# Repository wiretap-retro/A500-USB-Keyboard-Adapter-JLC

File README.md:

# A500 USB Keyboard Adapter JLC
A USB keyboard adapter for the Amiga 500 based on a simplified RP2040 design for JLCPCB Assembly

## Intro
This is a USB keyboard adapter I designed a board for to use in my Amiga 500 tower or bench testing. It is based on the amigahid-pico firmware by borb (nine). The KiCAD files, Gerbers, and BOM are in this repository, as well as the JLCPCB BOM and Pick'n'Place CPL files. The completed board attaches to the A500's keyboard header and provides a USB pin header for your interface device. On my build, I used a pin header to female USB Type A cable that screws into in the rear of my case on a PCI bracket.

Demo Video: https://youtu.be/7yw0AOvhLqg  (original board shown, this repository is an updated/simplified design for JLCPCB assembly)

## Parts
* In the Master BOM file, order the parts needed for hand soldering only. JLCPBC will do all the tough surface mount work. With 5 assembled boards, it comes out to roughly $15 each with shipping. (cheapest options / slow boat shipping)

## Building the Adapter
* Use JLCPCB's assembly service -- Upload the gerber files, choose your board color, and specify the Remove Order Number field as "Provided by Customer".
* Select the PCB Assembly slider and ensure you want either 2 or 5 boards assembled (top side only) and click confirm. Leave all other settings as-is.
* Click next at the board preview.
* On the Bill of Materials page, upload the BOM from the JLCPCB folder in this repo, as well as the Pick-n-Place CPL file. Click "Process BOM & CPL".
* Check to make sure all parts are available and click next, otherwise you have to substitute parts if a compatible part is in stock. (fit/form/function) Click next.
* On the Component Placement screen, ensure all parts are oriented and placed properly. Pay attention to Pin 1 on the chips. Click next.
* Choose the product type -- I recommend selecting "DIY". Save to cart and process your order. You may have to speak with JLCPCB to confirm your component placements via Email before they fully process it.
* Wait for your board to arrive.
* Solder the hand soldered components onto the board in their appropriate locations.

## Flashing the Firmware
First off, a huge thank you to Nine for developing the amigahid-pico, as this design uses its firmware. Firmware is located at: https://github.com/borb/amigahid-pico/
1. Build the firmware per the instructions at https://github.com/borb/amigahid-pico/blob/main/doc/installation.md
2. Hold the BOOT button.
3. Plug a MicroUSB cable to the PCB's MicroUSB port and plug the other end into the PC you just compiled the firmware on. It will then show up as a mass storage device.
4. Release the BOOT button.
5. Copy the amigahid-pico.uf2 file from the "build/src/" directory you compiled to the RP2040's mounted USB storage volume. It will then disconnect/reset.
6. Disconnect the USB cable from the PC and keyboard adapter PCB.

## Installation into the Amiga
1. Gain access to your Amiga 500 motherboard.
2. Disconnect the keyboard if it is still connected.
3. Plug the PCB into the A500's keyboard header either the Type A or Type B socket. For reference my Amiga 500 Rev 6A needed Type A.
4. Plug your USB cable into the pin header. Pay close attention to the orientation of the leads.
5. Plug the keyboard or wireless keyboard adapter into the other end of the USB cable. Don't use a blinding LED backlit keyboard that uses >500mA, as you don't want to smoke your traces.
6. Boot the Amiga and test it out!

## Optional Stuff
* If using a tower case, you can plug in the Power LED and HDD LED to the pin headers on the PCB to show the status indications.
* USB HID mouse support is included in Nine's firmware, but none of the mice I used would work with it. I use a DB9 connected OpenLaserMouse anyway, but maybe you'll have better luck testing various mice to see if one works. I know the firmware is still an in-progress project, or maybe I didn't do something right when I compiled the firmware. 
* Amiga keys are currently mapped to right and left windows keys. Before compiling the firmware, you can modify those keys if necessary at your own discretion.
* Reset is initiated by Left Ctrl + Left Win + Right Win (CTRL + AMIGA + AMIGA)

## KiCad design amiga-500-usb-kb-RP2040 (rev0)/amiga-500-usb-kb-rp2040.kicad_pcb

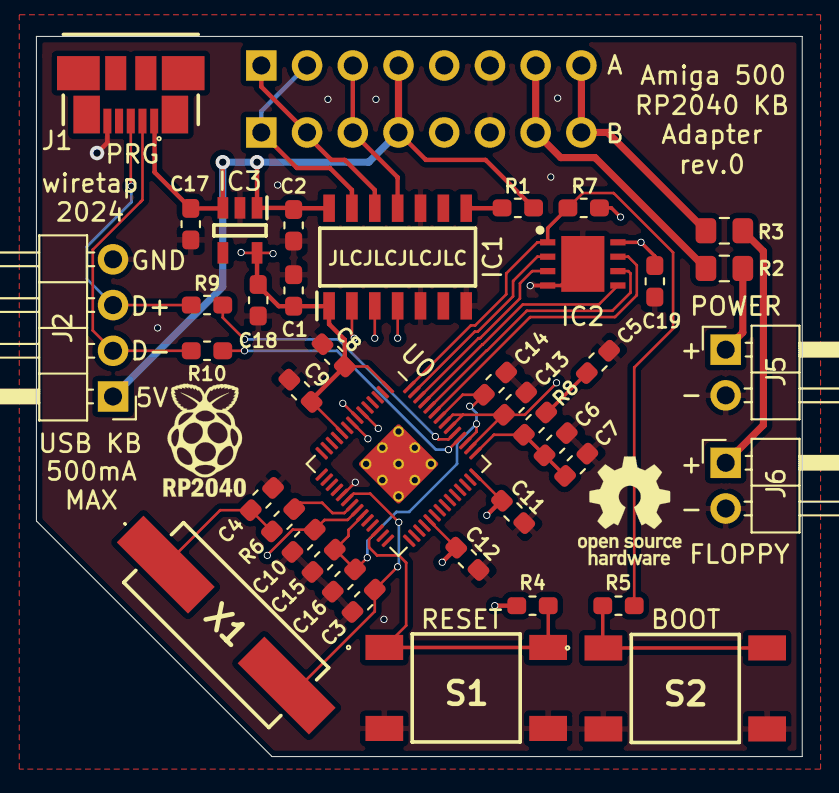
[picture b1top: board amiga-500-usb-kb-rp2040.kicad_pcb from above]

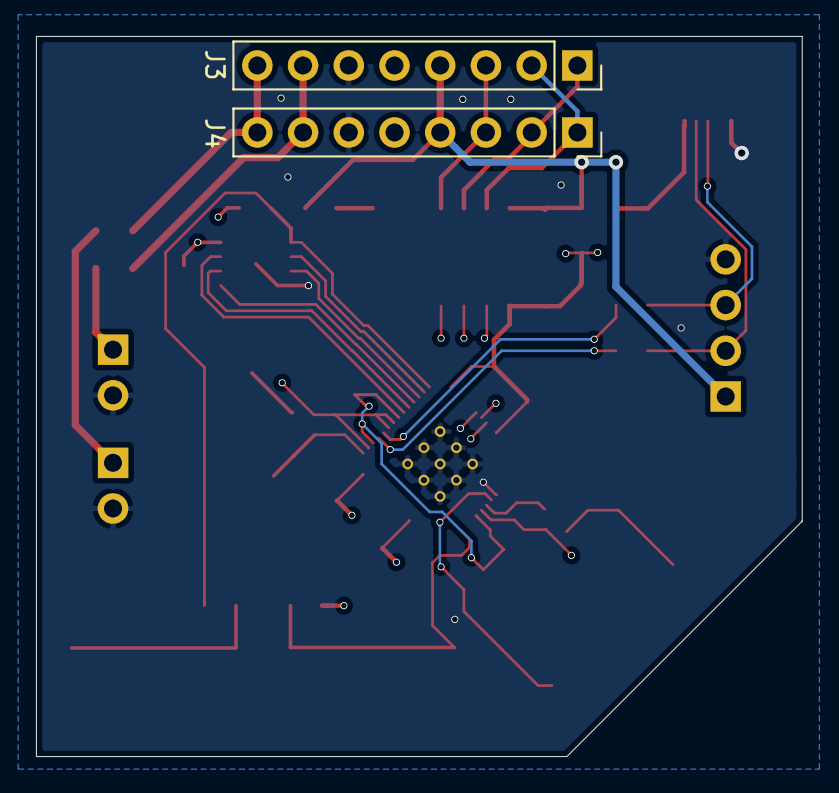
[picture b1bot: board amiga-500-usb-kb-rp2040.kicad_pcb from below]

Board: 4 copper layers, 42.5 x 40.0 mm, 42 parts (2 on the bottom side), 32 nets.

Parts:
C1, C2, C5, C6, C8, C9, C10, C11, C12, C14, C15, C19: 0.1uF; C_0603_1608Metric_Pad1.05x0.95mm_HandSolder
C3, C4: 27pF; C_0603_1608Metric_Pad1.05x0.95mm_HandSolder
C7, C13, C16, C17, C18: 1uF; C_0603_1608Metric_Pad1.05x0.95mm_HandSolder
IC1: TXS0104ED; SOIC127P600X175-14N
IC2: W25Q64JVXGIQ_TR; SON80P400X400X50-9N
IC3: TPS7A2033PDBVR; SOT95P280X145-5N
J1: 47346-0001
J2: USB_HEADER; PinHeader_1x04_P2.54mm_Horizontal
J3: Type A; PinSocket_1x08_P2.54mm_Vertical
J4: Type B; PinSocket_1x08_P2.54mm_Vertical
J5: Power LED; PinHeader_1x02_P2.54mm_Horizontal
J6: Floppy LED; PinHeader_1x02_P2.54mm_Horizontal
R1, R4, R7: 10k; R_0603_1608Metric_Pad1.05x0.95mm_HandSolder
R2, R3: 1k; R_0805_2012Metric_Pad1.15x1.40mm_HandSolder
R5, R6: 1k; R_0603_1608Metric_Pad1.05x0.95mm_HandSolder
R8, R9, R10: 27; R_0603_1608Metric_Pad1.05x0.95mm_HandSolder
S1, S2: FSM2JSMAATR; FSM2J_1
U0: RP2040; RP2040-QFN-56
X1: ABLS-12MHZ-B4-T; ABLS

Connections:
+3V3: C1.1, C8.1, C9.1, C10.1, C11.1, C12.1, C13.1, C18.1, C19.1, IC1.1, IC2.8, IC3.5, R4.1, R7.1, U0.1, U0.10, U0.22, U0.33, U0.42, U0.44, U0.48, U0.49
+5V: C2.2, C17.1, IC1.14, IC3.1, IC3.3, J1.1, J2.1, J3.4, J4.4, R1.1
FLOPPY_LED: J3.8, J4.8, R3.2
GND: C1.2, C2.1, C3.2, C4.2, C5.2, C6.2, C7.2, C8.2, C9.2, C10.2, C11.2, C12.2, C13.2, C14.2, C15.2, C16.2, C17.2, C18.2, C19.2, IC1.5, IC1.7, IC1.10, IC2.4, IC2.9, IC3.2, J1.5, J2.4, J3.6, J4.6, J5.2, J6.2, S1.3, S1.4, S2.3, S2.4, U0.19, U0.57
KB_CLK: IC1.3, U0.8
KB_CLK_RAW: IC1.12, J3.1, J4.2
KB_DATA: IC1.2, U0.7
KB_DATA_RAW: IC1.13, J3.2, J4.1
KB_RESET: IC1.4, U0.6
KB_RESET_RAW: IC1.11, J3.3, J4.3
unnamed: C3.1, U0.20, X1.2
unnamed: C4.1, R6.1, X1.1
unnamed: C5.1, R8.2
unnamed: C6.1, C7.1, R8.1, U0.43
unnamed: C14.1, C15.1, C16.1, U0.23, U0.45, U0.50
unnamed: IC1.8, R1.2
unnamed: J5.1, R2.1
unnamed: J6.1, R3.1
unnamed: R4.2, S1.1, S1.2, U0.26
unnamed: R5.1, S2.1, S2.2
unnamed: R6.2, U0.21
unnamed: R9.2, U0.47
unnamed: R10.1, U0.46
PWR_LED: J3.7, J4.7, R2.2
QSPI_CS: IC2.1, R5.2, R7.2, U0.56
QSPI_SCLK: IC2.6, U0.52
QSPI_SD0: IC2.5, U0.53
QSPI_SD1: IC2.2, U0.55
QSPI_SD2: IC2.3, U0.54
QSPI_SD3: IC2.7, U0.51
USB_DM: J1.2, J2.2, R10.2
USB_DP: J1.3, J2.3, R9.1

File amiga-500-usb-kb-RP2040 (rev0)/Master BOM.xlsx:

Reference | Quantity | Value | Footprint | Manufacturer Name | Part Number | Mouser Part Number | LCSC Part Number | Comment
C1 C2 C15 C14 C12 C11 C10 C9 C8 C6 C5 C19 | 12 | 0.1uF | Capacitor_SMD:C_0603_1608Metric_Pad1.05x0.95mm_HandSolder | KYOCERA AVX | 06035C104KAT2A | 581-06035C104KAT2A | C14663 | Use JLCPCB / LCSC Assembly
C16 C13 C7 C17 C18 | 5 | 1uF | Capacitor_SMD:C_0603_1608Metric_Pad1.05x0.95mm_HandSolder | KYOCERA AVX | 0603YC105KAT2A | 581-0603YC105KAT2A | C86020 | Use JLCPCB / LCSC Assembly
C3 C4 | 2 | 27pF | Capacitor_SMD:C_0603_1608Metric_Pad1.05x0.95mm_HandSolder | KYOCERA AVX | 06035A270JAT4A | 581-06035A270JAT4A | C92670 | Use JLCPCB / LCSC Assembly
IC1 | 1 | TXS0104ED | SamacSys_Parts:SOIC127P600X175-14N | Texas Instruments | TXS0104ED | 595-TXS0104ED | C79342 | Use JLCPCB / LCSC Assembly
IC2 | 1 | W25Q64JVXGIQ_TR | SamacSys_Parts:SON80P400X400X50-9N | Winbond | W25Q64JVXGIQ TR | 454-W25Q64JVXGIQTR | C2940195 | Use JLCPCB / LCSC Assembly
IC3 | 1 | TPS7A2033PDBVR | SamacSys_Parts:SOT95P280X145-5N | Texas Instruments | TPS7A2033PDBVR | 595-TPS7A2033PDBVR | C2862740 | Use JLCPCB / LCSC Assembly
J1 | 1 | 47346-0001 | 47346-0001 | Molex | 47346-0001 | 538-47346-0001 | C132560 | Use JLCPCB / LCSC Assembly
J2 | 1 | USB_HEADER | Connector_PinHeader_2.54mm:PinHeader_1x04_P2.54mm_Horizontal | Amphenol FCI | 10129379-904002BLF | 649-1012937990402BLF | C492412 | Hand Solder
J3 | 1 | Type A | Connector_PinSocket_2.54mm:PinSocket_1x08_P2.54mm_Vertical | TE Connectivity | 534237-6 | 571-5342376 | C2897371 | Hand Solder
J4 | 1 | Type B | Connector_PinSocket_2.54mm:PinSocket_1x08_P2.54mm_Vertical | TE Connectivity | 534237-6 | 571-5342376 | C2897371 | Hand Solder
J5 | 1 | Power LED | Connector_PinHeader_2.54mm:PinHeader_1x02_P2.54mm_Horizontal | Amphenol FCI | 10129379-902002BLF | 649-1012937990202BLF | C492410 | Hand Solder
J6 | 1 | Floppy LED | Connector_PinHeader_2.54mm:PinHeader_1x02_P2.54mm_Horizontal | Amphenol FCI | 10129379-902002BLF | 649-1012937990202BLF | C492410 | Hand Solder
R1 R4 R7 | 3 | 10k | Resistor_SMD:R_0603_1608Metric_Pad1.05x0.95mm_HandSolder | Bourns | CR0603-FX-1002ELF | 652-CR0603FX-1002ELF | C98220 | Use JLCPCB / LCSC Assembly
R2 R3 | 2 | 1k | Resistor_SMD:R_0805_2012Metric_Pad1.15x1.40mm_HandSolder | Vishay | CRCW08051K00FKEAHP | 71-CRCW08051K00FKEAH | C160065 | Use JLCPCB / LCSC Assembly
R5 R6 | 2 | 1k | Resistor_SMD:R_0603_1608Metric_Pad1.05x0.95mm_HandSolder | Vishay | MCT06030C1001FPW00 | 594-MCT06030C1001FPW | C22548 | Use JLCPCB / LCSC Assembly
R9 R10 R8 | 3 | 27 | Resistor_SMD:R_0603_1608Metric_Pad1.05x0.95mm_HandSolder | Yageo | RC0603FR-0727RL | 603-RC0603FR-0727RL | C137753 | Use JLCPCB / LCSC Assembly
S1 S2 | 2 | FSM2JSMAATR | SamacSys_Parts:FSM2J_1 | TE Connectivity | FSM2JSMAATR | 506-FSM2JSMAATR | C86487 | Use JLCPCB / LCSC Assembly
U0 | 1 | RP2040 | SamacSys_Parts:RP2040-QFN-56 | Raspberry Pi | SC0914(13) | 358-SC091413 | C2040 | Use JLCPCB / LCSC Assembly
X1 | 1 | ABLS-12MHZ-B4-T | SamacSys_Parts:ABLS | ABRACON | ABLS-12.000MHZ-B4-T | 815-ABLS-12.0M-T | C326543 | Use JLCPCB / LCSC Assembly
